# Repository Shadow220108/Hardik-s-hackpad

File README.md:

# Hardik's-hackpad
Its my personal hackpad made with the help of hack club 

# This will be the design of my hackpad/macropad  

# These are the bottom and top cases  

# This is the schematic  

# This is the PCB  

# 🛠️ Hardware Bill of Materials (BOM)  
Seeed XIAO RP2040 - x1  
Through-hole 1N4148 Diodes - x8  
MX-Style switches - x8  
EC11 Rotary encoders - x1  
Blank DSA keycaps - x8  
SK6812 MINI-E LEDs - x8  
M3x16mm Screws & M3 Heatset Inserts - x4

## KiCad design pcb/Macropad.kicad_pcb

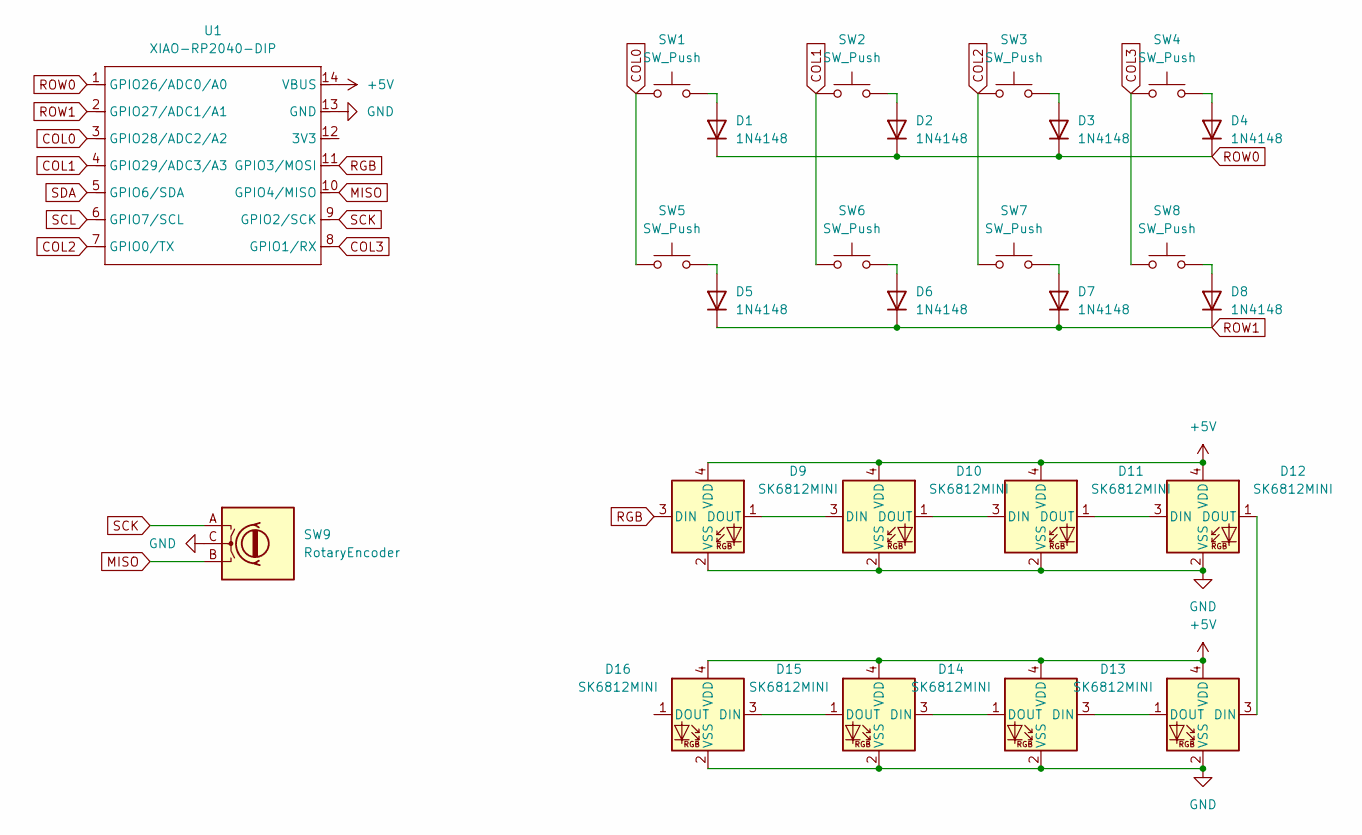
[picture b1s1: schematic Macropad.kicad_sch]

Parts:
D1, D2, D3, D4, D5, D6, D7, D8: 1N4148; D_DO-35_SOD27_P7.62mm_Horizontal
D9, D10, D11, D12, D13, D14, D15, D16: SK6812MINI; LED_SK6812MINI_PLCC4_3.5x3.5mm_P1.75mm
SW1, SW2, SW3, SW4, SW5, SW6, SW7, SW8: SW_Push; SW_Cherry_MX_1.00u_PCB
SW9: RotaryEncoder; RotaryEncoder_Alps_EC11E-Switch_Vertical_H20mm
U1: XIAO-RP2040-DIP; XIAO-RP2040-SMD

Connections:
+5V: D9.4 (VDD), D10.4 (VDD), D11.4 (VDD), D12.4 (VDD), D13.4 (VDD), D14.4 (VDD), D15.4 (VDD), D16.4 (VDD), U1.14 (VBUS)
COL0: SW1.1, SW5.1, U1.3 (GPIO28/ADC2/A2)
COL1: SW2.1, SW6.1, U1.4 (GPIO29/ADC3/A3)
COL2: SW3.1, SW7.1, U1.7 (GPIO0/TX)
COL3: SW4.1, SW8.1, U1.8 (GPIO1/RX)
GND: D9.2 (VSS), D10.2 (VSS), D11.2 (VSS), D12.2 (VSS), D13.2 (VSS), D14.2 (VSS), D15.2 (VSS), D16.2 (VSS), SW9.C, U1.13 (GND)
MISO: SW9.B, U1.10 (GPIO4/MISO)
unnamed: D1.2 (A), SW1.2
unnamed: D2.2 (A), SW2.2
unnamed: D3.2 (A), SW3.2
unnamed: D4.2 (A), SW4.2
unnamed: D5.2 (A), SW5.2
unnamed: D6.2 (A), SW6.2
unnamed: D7.2 (A), SW7.2
unnamed: D8.2 (A), SW8.2
unnamed: D9.1 (DOUT), D10.3 (DIN)
unnamed: D10.1 (DOUT), D11.3 (DIN)
unnamed: D11.1 (DOUT), D12.3 (DIN)
unnamed: D12.1 (DOUT), D13.3 (DIN)
unnamed: D13.1 (DOUT), D14.3 (DIN)
unnamed: D14.1 (DOUT), D15.3 (DIN)
unnamed: D15.1 (DOUT), D16.3 (DIN)
RGB: D9.3 (DIN), U1.11 (GPIO3/MOSI)
ROW0: D1.1 (K), D2.1 (K), D3.1 (K), D4.1 (K), U1.1 (GPIO26/ADC0/A0)
ROW1: D5.1 (K), D6.1 (K), D7.1 (K), D8.1 (K), U1.2 (GPIO27/ADC1/A1)
SCK: SW9.A, U1.9 (GPIO2/SCK)
SCL: U1.6 (GPIO7/SCL)
SDA: U1.5 (GPIO6/SDA)
VCC: U1.12 (3V3)

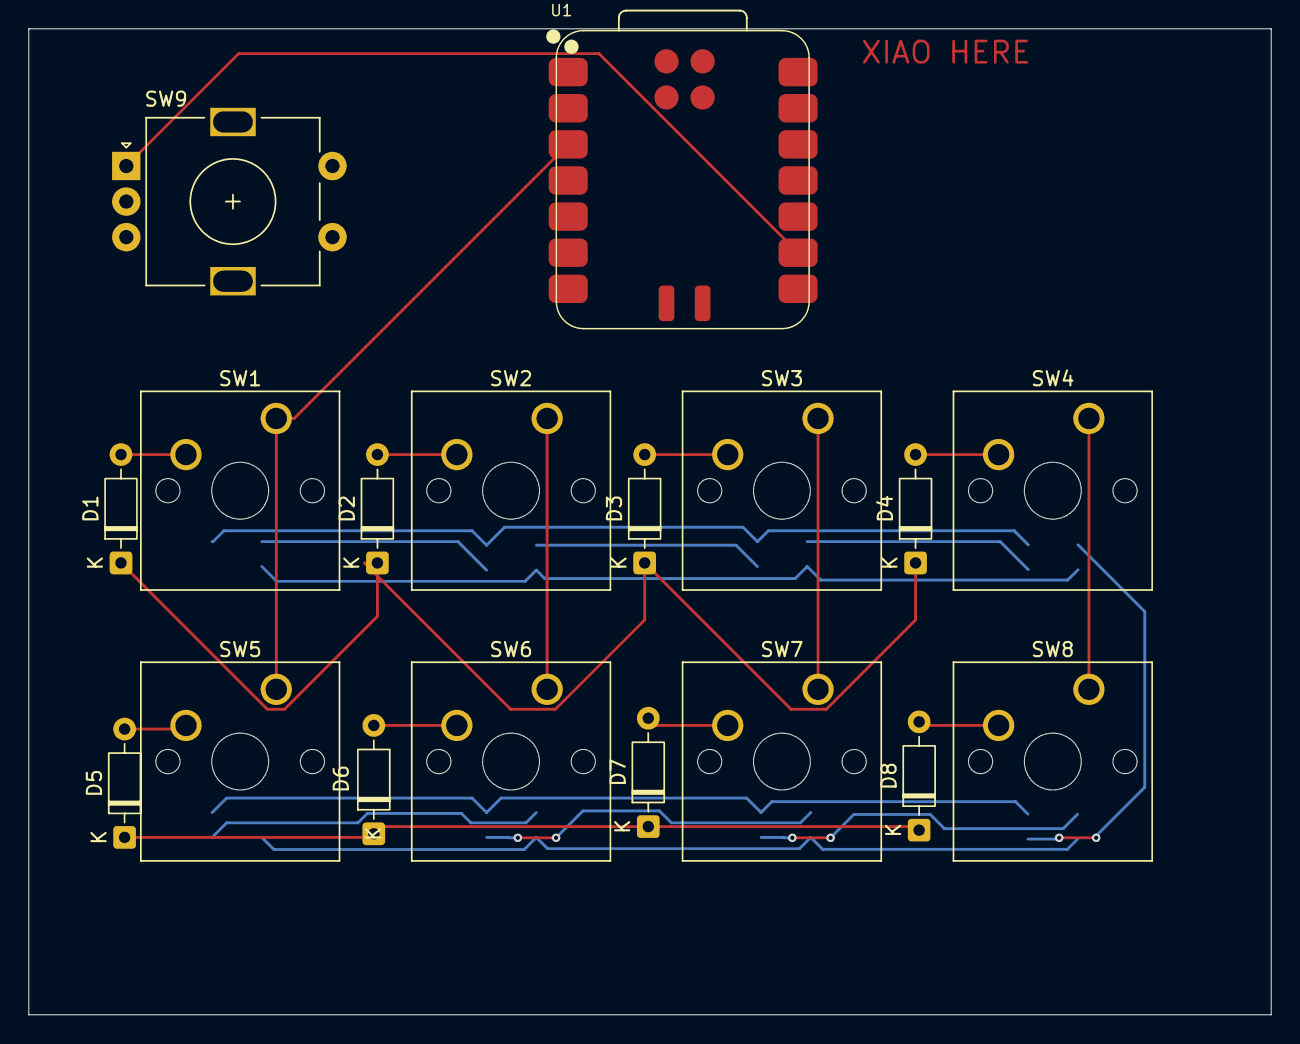
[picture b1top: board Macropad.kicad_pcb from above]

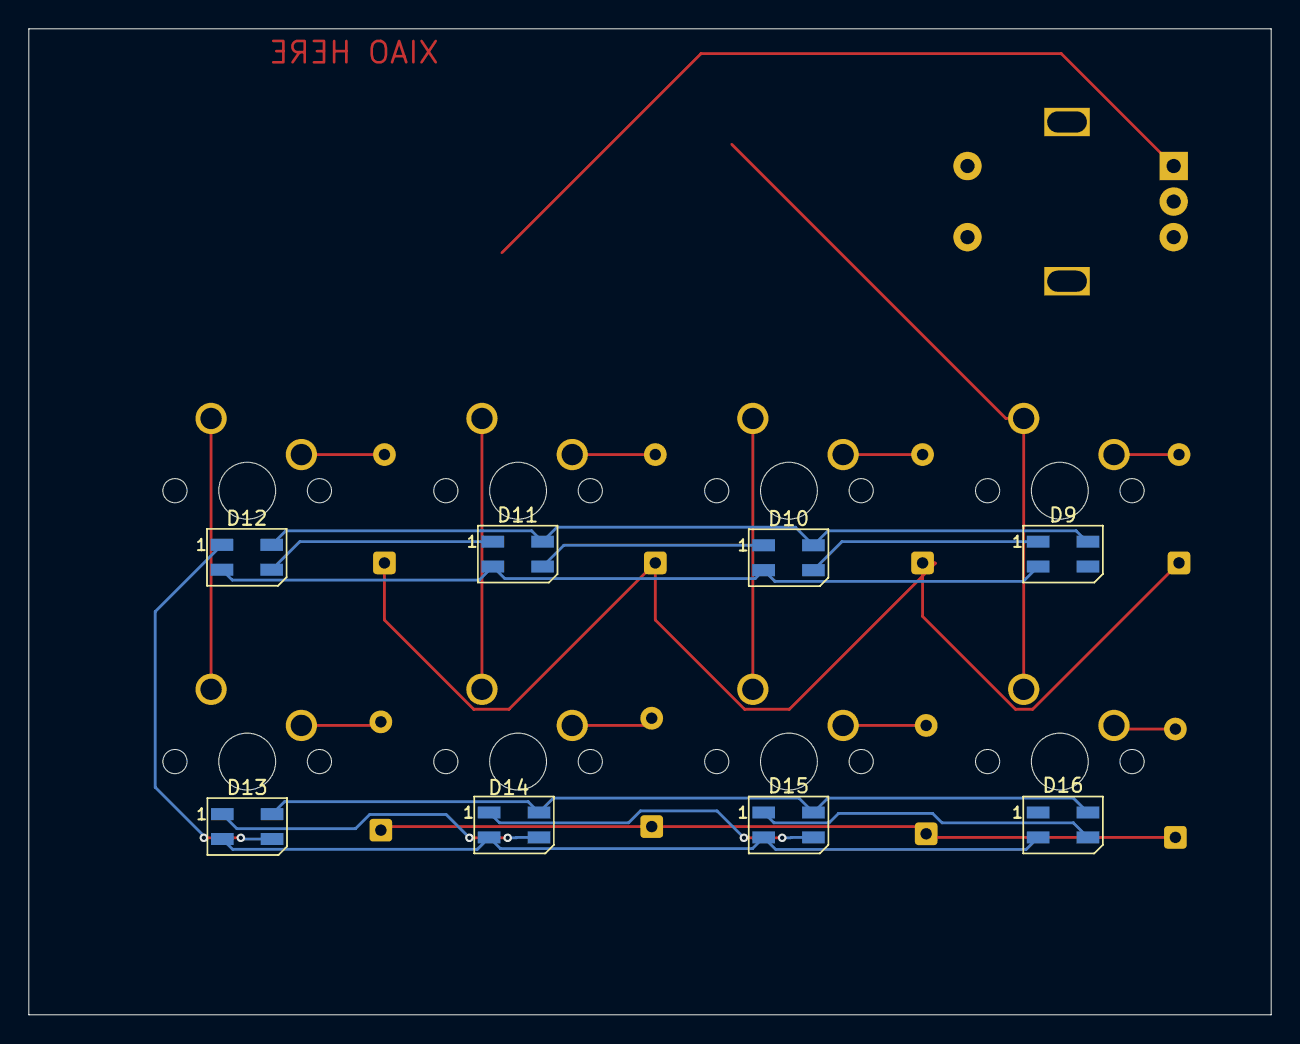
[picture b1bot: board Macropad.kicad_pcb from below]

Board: 2 copper layers, 87.4 x 69.3 mm, 26 parts (8 on the bottom side), 26 nets.
